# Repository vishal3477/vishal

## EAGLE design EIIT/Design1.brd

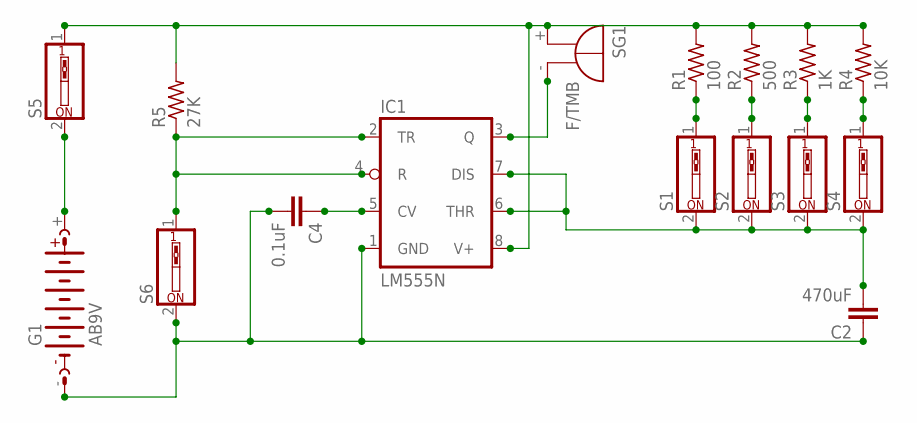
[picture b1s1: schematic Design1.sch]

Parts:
C2: 470uF; C5B2.5
C4: 0.1uF; C5B2.5
G1: AB9V
IC1: LM555N; DIL08
R1: 100; 0207/12
R2: 500; 0207/12
R3: 1K; 0207/12
R4: 10K; 0207/12
R5: 27K; 0207/12
S1, S2, S3, S4, S5, S6: SW_DIP-1; EDG-01
SG1: F/TMB

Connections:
unnamed: IC1.8 (V+), R1.2, R2.2, R3.2, R4.2, R5.2, S5.1, SG1.+
unnamed: R1.1, S1.1
unnamed: C2.2, IC1.6 (THR), IC1.7 (DIS), S1.2, S2.2, S3.2, S4.2
unnamed: C4.1, IC1.5 (CV)
unnamed: R2.1, S2.1
unnamed: R3.1, S3.1
unnamed: IC1.2 (TR), IC1.4 (R), R5.1, S6.1
unnamed: IC1.3 (Q), SG1.-
unnamed: R4.1, S4.1
unnamed: G1.+, S5.2
unnamed: C2.1, C4.2, G1.-, IC1.1 (GND), S6.2

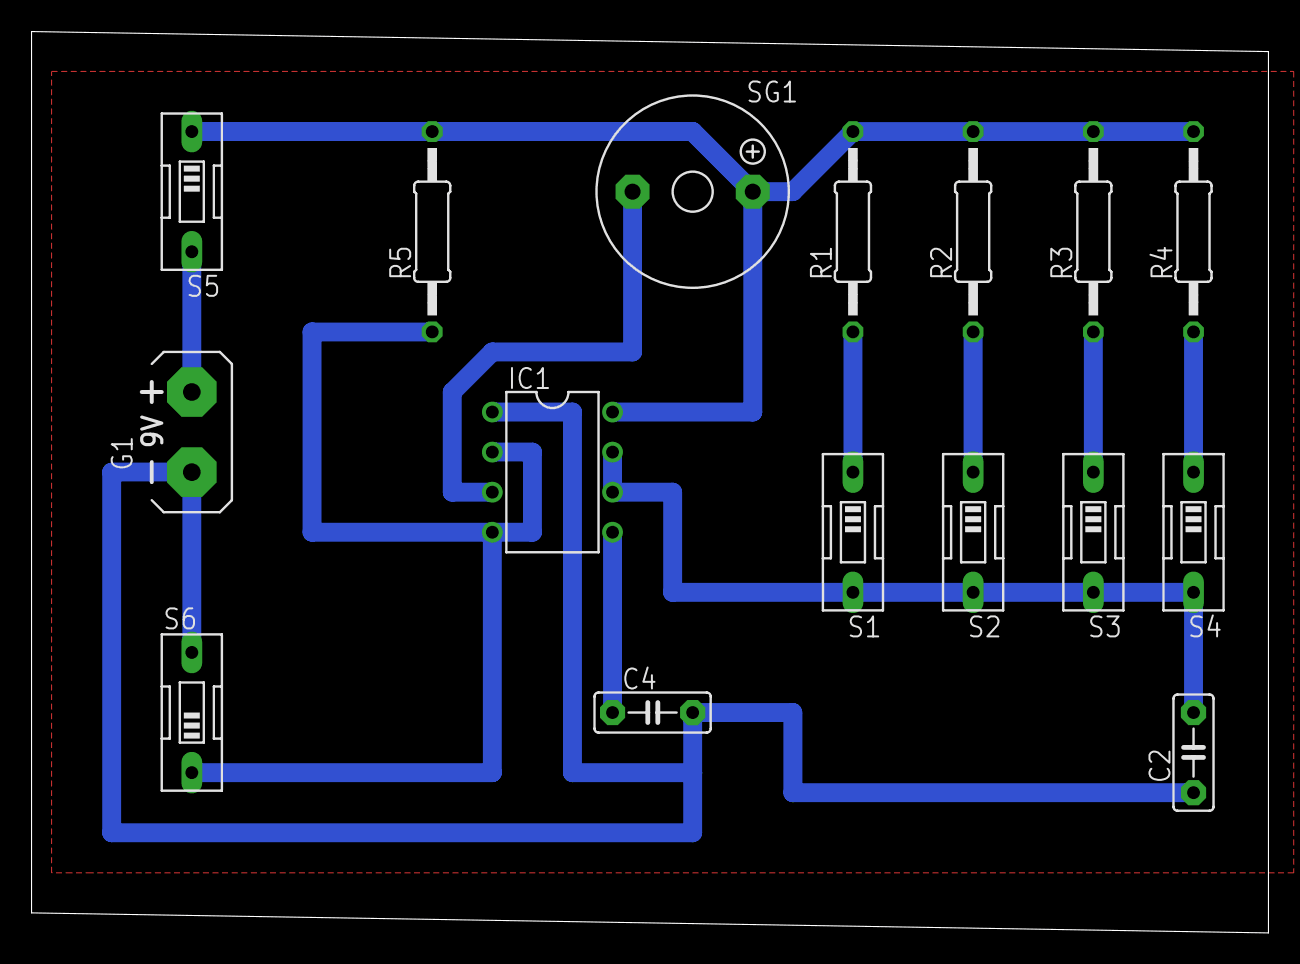
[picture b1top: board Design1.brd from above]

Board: 2 copper layers, 78.4 x 57.1 mm, 16 parts (0 on the bottom side), 11 nets.
